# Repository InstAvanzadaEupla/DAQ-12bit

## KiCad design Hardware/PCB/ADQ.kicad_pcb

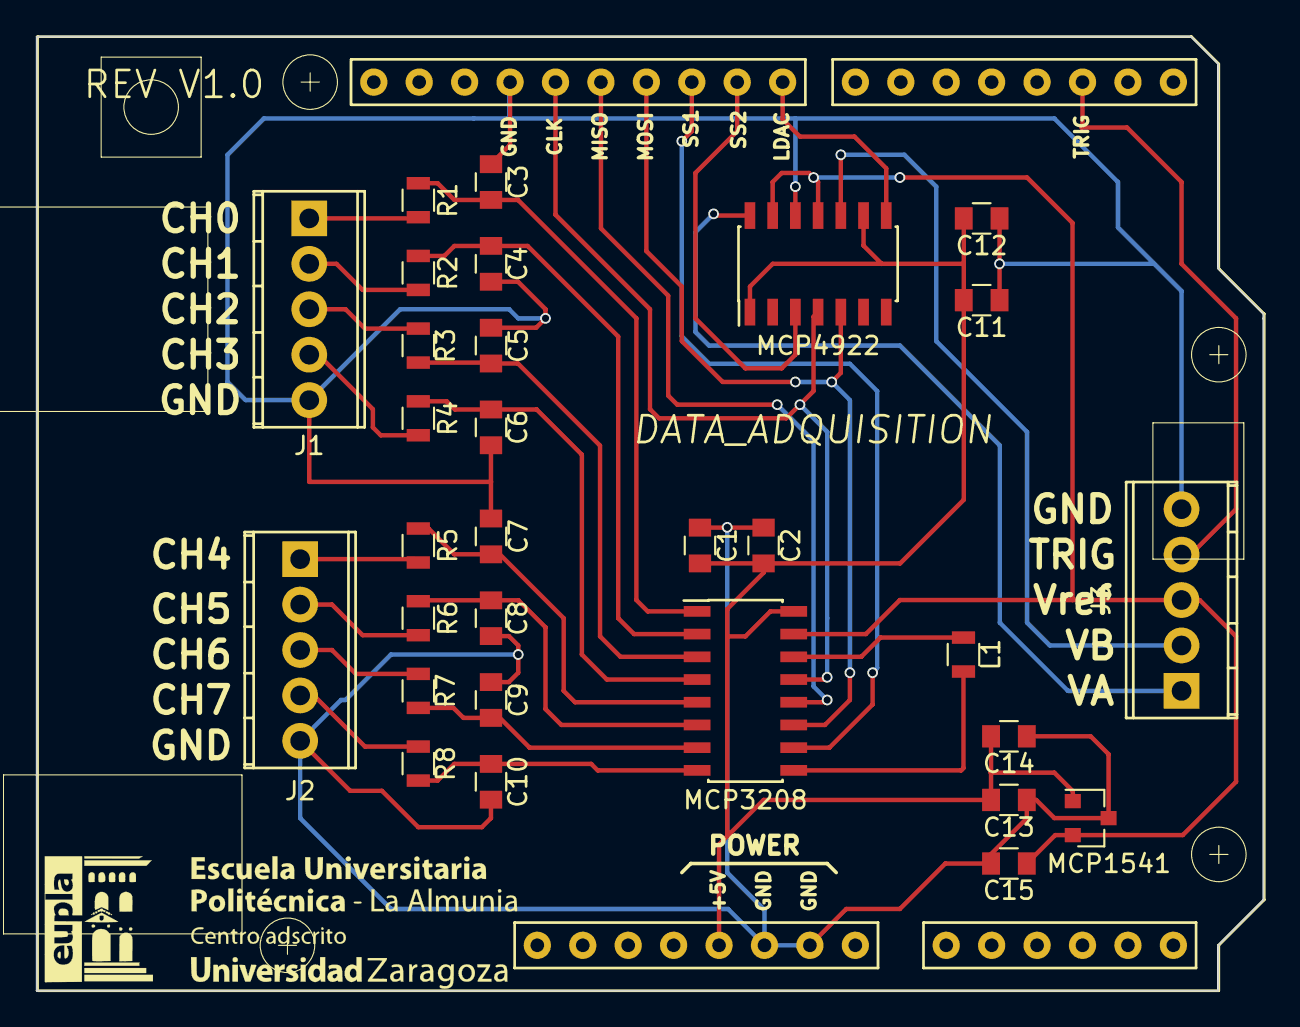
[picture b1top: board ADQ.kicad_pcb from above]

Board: 2 copper layers, 68.6 x 53.3 mm, 31 parts (0 on the bottom side), 30 nets.

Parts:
C1, C13, C15: 10uF; C_0805
C2, C14: 0.1uF; C_0805
C3, C4, C5, C6, C7, C8, C9, C10: 100nF; C_0805
C11: 10nF; C_0805
C12: 0.1nF; C_0805
J1, J2, J3: Conn_01x05; TerminalBlock_Phoenix_MPT-2.54mm_5pol
L1: Ferrite_Bead; L_0805
MCP1541: MCP1541; SOT-23
MCP3208: MCP3208; SOIC-16_3.9x9.9mm_Pitch1.27mm
MCP4922: MCP4922; SOIC-14_3.9x8.7mm_Pitch1.27mm
R1, R2, R3, R4, R5, R6, R7, R8: 330R; R_0805
REV V1.0: DATA_ADQUISITION; ARDUINO_as_UNO_R3_CONTOUR

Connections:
+5V: C1.1, C2.1, C11.1, C12.1, C13.1, C14.1, MCP1541.1, MCP3208.16, MCP4922.1, MCP4922.9, REV V1.0.5V
/ADC/CH0: J1.1, R1.2
/ADC/CH1: J1.2, R2.2
/ADC/CH2: J1.3, R3.2
/ADC/CH3: J1.4, R4.2
/ADC/CH4: J2.1, R5.2
/ADC/CH5: J2.2, R6.2
/ADC/CH6: J2.3, R7.2
/ADC/CH7: J2.4, R8.2
/ADC/Vref: C15.1, J3.3, MCP1541.2, MCP3208.15, MCP4922.11, MCP4922.13
/CLK: MCP3208.13, MCP4922.4, REV V1.0.13
/LDAC: MCP4922.8, REV V1.0.8
/MISO: MCP3208.12, REV V1.0.12
/MOSI: MCP3208.11, MCP4922.5, REV V1.0.11
/SS1: MCP3208.10, REV V1.0.10
/SS2: MCP4922.3, REV V1.0.9
/TRIG: J3.4, REV V1.0.2
/VoutA: J3.1, MCP4922.14
/VoutB: J3.2, MCP4922.10
GND: C1.2, C2.2, C3.2, C4.2, C5.2, C6.2, C7.2, C8.2, C9.2, C10.2, C11.2, C12.2, C13.2, C14.2, C15.2, J1.5, J2.5, J3.5, MCP1541.3, MCP4922.12, REV V1.0.GND1, REV V1.0.GND2, REV V1.0.GND3
GNDA: L1.2, MCP3208.14
GNDD: L1.1, MCP3208.9
unnamed: C3.1, MCP3208.1, R1.1
unnamed: C4.1, MCP3208.2, R2.1
unnamed: C5.1, MCP3208.3, R3.1
unnamed: C6.1, MCP3208.4, R4.1
unnamed: C7.1, MCP3208.5, R5.1
unnamed: C8.1, MCP3208.6, R6.1
unnamed: C9.1, MCP3208.7, R7.1
unnamed: C10.1, MCP3208.8, R8.1

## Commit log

2018-03-21 V0.1
